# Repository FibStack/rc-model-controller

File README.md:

# RC Transmitter Receiver System

## Overview

This project has the design files for a custom Remote Control (RC) system that you can use to control different models. The design files include:

- Schematics and PCB design for the transmitter and receiver boards.
- The source code for the microcontrollers on the transmitter and receiver boards.
- A sample 3D printable model for an RC car.

Please note that this is just the initial proof of concept, and more updates are on the way to make it even better.

## Project organization

- **hardware/** - In this folder, you'll find the circuit schematics and PCB design files for both the receiver and transmitter boards.
- **software/attiny824-transmiter** - This contains the source code for the ATTiny824 chip on the transmitter board.
- **software/attiny824-receiver** - Here, you'll find the source code for the ATTiny824 chip on the receiver board.
- **rc-car-frame.FCStd** - This file holds a 3D model of an RC car frame that we used for testing in this project.

## Development tools

- **[Microchip Studio 7.0](https://www.microchip.com/en-us/tools-resources/develop/microchip-studio)**: The IDE for writing and building source code for the ATTiny chip. We also use this tool to flash the chips.
- **[ATMEL-ICE](https://www.microchip.com/en-us/development-tool/ATATMEL-ICE)**: Hardware tool for flashing ATTiny chips.
- **[KiCad EDA](https://www.kicad.org/)**: The application for schematic and PCB design.
- **[FreeCAD](https://www.freecad.org/)**: The application for parametric desing used to desing the model.

To build the ATTiny824 firmware, open the project in Microchip Studio. Build the solution to generate the `*.HEX` file. Next, use the appropriate tool available to flash the chip.

## BOM
| # | Components | Recommended models | Footprint | Quantity |
| --- | --- | --- | --- | --- |
| 1 | PCB | Recommended two-layer PCB board of 1.6 mm thickness | | 1 |
| 2 | U1, U2 | ATtiny824 | SOIC-14 | 2 |
| 3 | C1, C2 | 100nF | 0603 (1608 metric) | 2 |
| 4 | D1, D3 | SMD LED | 0603 (1608 metric) | 2 |
| 5 | D2, D4 | SMD Generic diode | MicroMELF | 2 |
| 6 | Q1-Q6 | 2N7002 | SOT-23 | 6 |
| 7 | R1, R2, R4, R5, R6, R7, R9, R12, R13, R18, R19, R20  | 10K | 0603 (1608 metric) | 12 |
| 8 | R3, R14  | 470 | 0603 (1608 metric) | 2 |
| 9 | R8, R10, R11, R15, R16, R17  | 100 | 0603 (1608 metric) | 6 |
| 10 | RV1 | 10K Slide Potentiometer | PTA1543 | 1 |
| 11 | RV2 | 10K Potentiometer | T-16H Single Horizontal | 1 |
| 12 | SW1, SW2, SW3, SW4, SW5, SW6 | SPDT Slide Switch | P2.54mm | 6 |
| 13 | J1 | Male Header Connector, 1x3, pitch 2.54mm | 	1x3 - P2.54mm | 1 |
| 14 | J2, J5, J6, J7, J9, J10, J11, J12, J13, J14, J15, J17, J18, J19 | Male Header Connector, 1x2, pitch 2.54mm | 	1x2 - P2.54mm | 14 |
| 15 | J3, J16 | Male Header Connector, 2x3, pitch 2.54mm | 	2x3 - P2.54mm | 2 |
| 16 | J8 | Male Header Connector, 1x4, pitch 2.54mm | 	1x4 - P2.54mm | 1 |

## Documentation

For more detailed information about the project, please visit the [project page](https://fibstack.com/projects/rc-model-controller/).

## License Information
This product is open source!

Please review the LICENSE.md file for license information. Distributed as-is; no warranty is given.

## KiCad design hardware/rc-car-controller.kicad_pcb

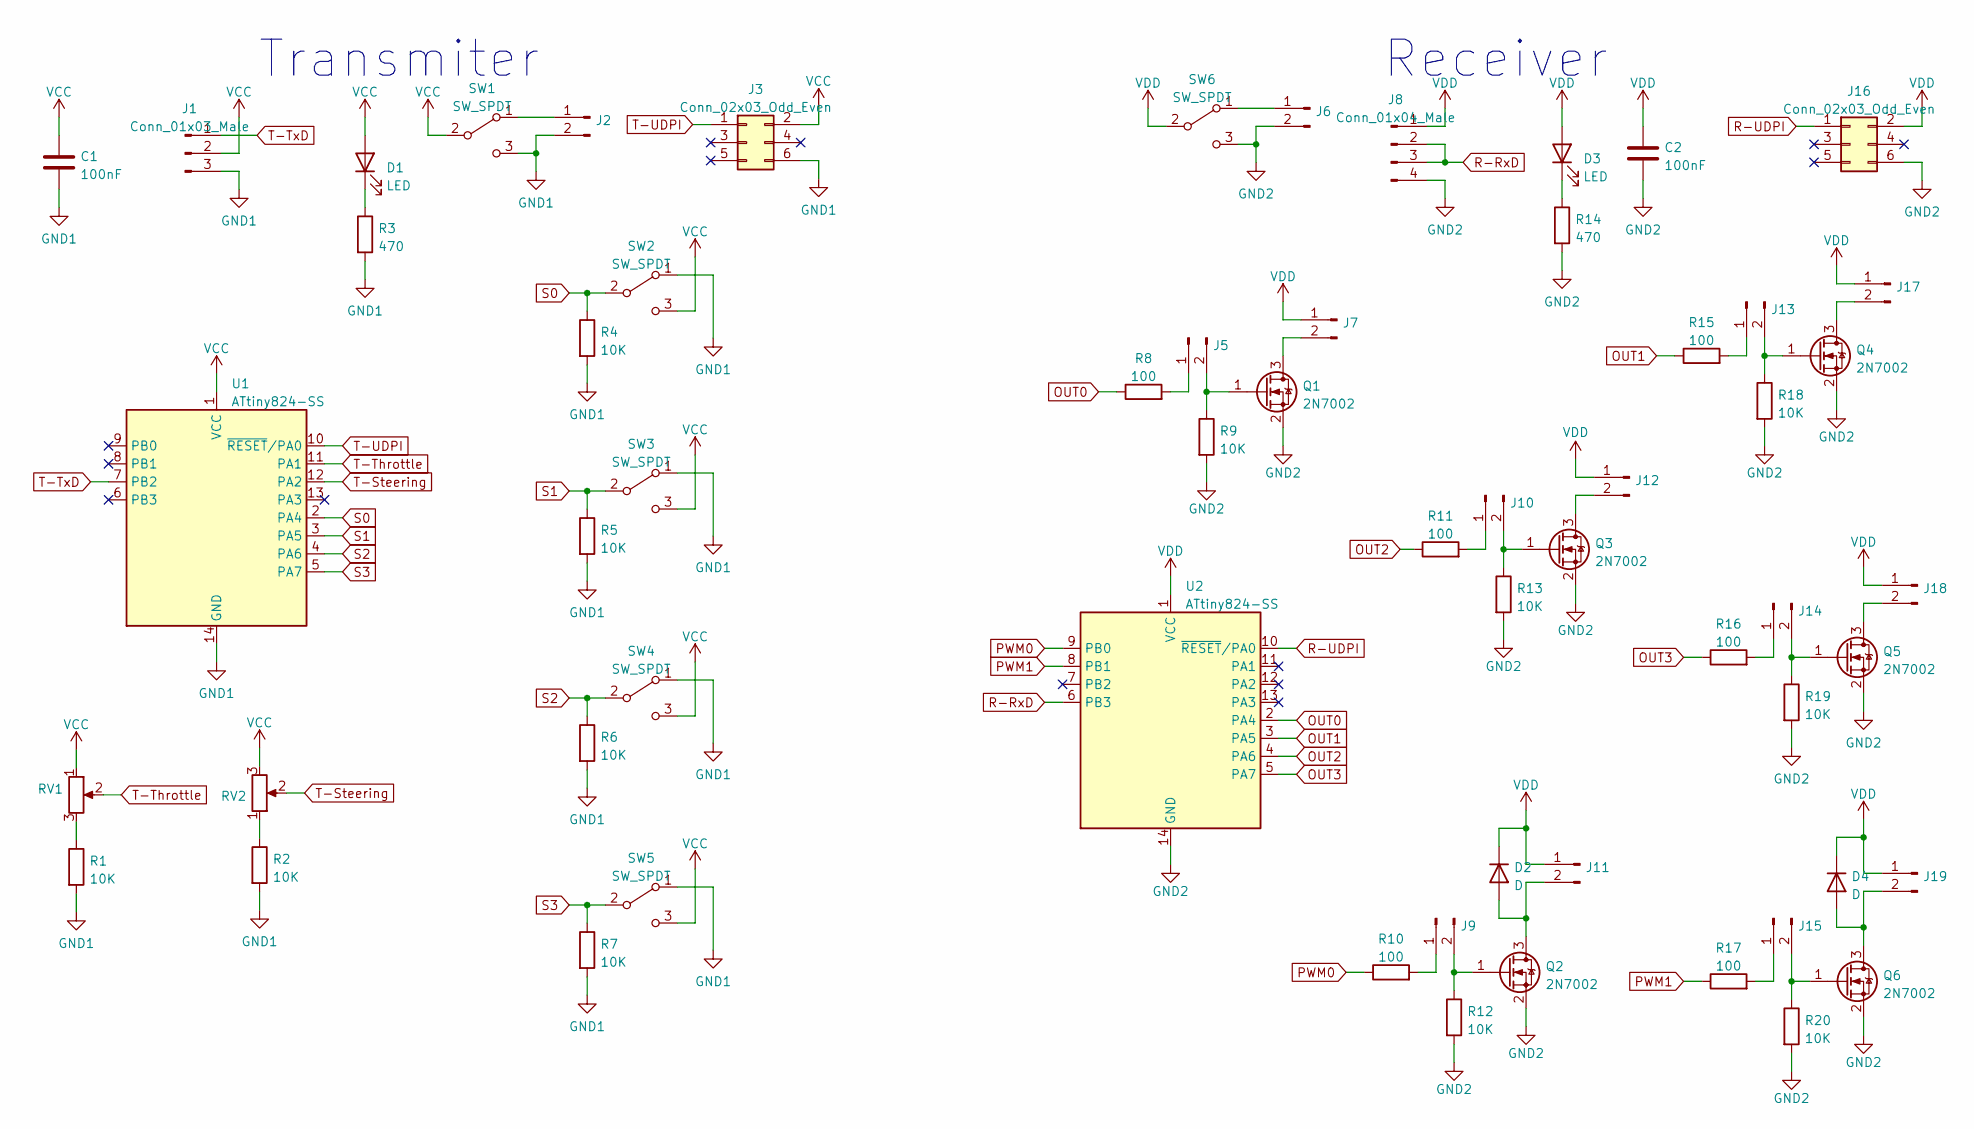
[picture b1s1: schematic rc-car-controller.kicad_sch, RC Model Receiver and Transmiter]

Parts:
C1, C2: 100nF; C_0603_1608Metric
D1, D3: LED; D_0603_1608Metric
D2, D4: D; D_MicroMELF
J1: Conn_01x03_Male; PinHeader_1x03_P2.54mm_Vertical
J2, J5, J6, J7, J9, J10, J11, J12, J13, J14, J15, J17, J18, J19: Conn_01x02_Male; PinHeader_1x02_P2.54mm_Vertical
J3, J16: Conn_02x03_Odd_Even; PinHeader_2x03_P2.54mm_Vertical
J8: Conn_01x04_Male; PinHeader_1x04_P2.54mm_Vertical
Q1, Q2, Q3, Q4, Q5, Q6: 2N7002; SOT-23
R1, R2, R4, R5, R6, R7, R9, R12, R13, R18, R19, R20: 10K; R_0603_1608Metric
R3, R14: 470; R_0603_1608Metric
R8, R10, R11, R15, R16, R17: 100; R_0603_1608Metric
RV1: R_Potentiometer; Potentiometer_Bourns_PTA1543_Single_Slide
RV2: R_Potentiometer; Potentiometer_Piher_T-16H_Single_Horizontal
SW1, SW2, SW3, SW4, SW5, SW6: SW_SPDT; PinHeader_1x03_P2.54mm_Vertical
U1, U2: ATtiny824-SS; SOIC-14_3.9x8.7mm_P1.27mm

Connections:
GND1: C1.2, J1.3, J2.2, J3.6, R1.2, R2.2, R3.2, R4.2, R5.2, R6.2, R7.2, SW1.3 (C), SW2.1 (A), SW3.1 (A), SW4.1 (A), SW5.1 (A), U1.14 (GND)
GND2: C2.2, J6.2, J8.4, J16.6, Q1.2 (S), Q2.2 (S), Q3.2 (S), Q4.2 (S), Q5.2 (S), Q6.2 (S), R9.2, R12.2, R13.2, R14.2, R18.2, R19.2, R20.2, SW6.3 (C), U2.14 (GND)
unnamed: D1.1 (K), R3.1
unnamed: D2.2 (A), J11.2, Q2.3 (D)
unnamed: D3.1 (K), R14.1
unnamed: D4.2 (A), J19.2, Q6.3 (D)
unnamed: J2.1, SW1.1 (A)
unnamed: J5.1, R8.2
unnamed: J5.2, Q1.1 (G), R9.1
unnamed: J6.1, SW6.1 (A)
unnamed: J7.2, Q1.3 (D)
unnamed: J9.1, R10.2
unnamed: J9.2, Q2.1 (G), R12.1
unnamed: J10.1, R11.2
unnamed: J10.2, Q3.1 (G), R13.1
unnamed: J12.2, Q3.3 (D)
unnamed: J13.1, R15.2
unnamed: J13.2, Q4.1 (G), R18.1
unnamed: J14.1, R16.2
unnamed: J14.2, Q5.1 (G), R19.1
unnamed: J15.1, R17.2
unnamed: J15.2, Q6.1 (G), R20.1
unnamed: J17.2, Q4.3 (D)
unnamed: J18.2, Q5.3 (D)
unnamed: R1.1, RV1.3
unnamed: R2.1, RV2.1
OUT0: R8.1, U2.2 (PA4)
OUT1: R15.1, U2.3 (PA5)
OUT2: R11.1, U2.4 (PA6)
OUT3: R16.1, U2.5 (PA7)
PWM0: R10.1, U2.9 (PB0)
PWM1: R17.1, U2.8 (PB1)
R-RxD: J8.2, J8.3, U2.6 (PB3)
R-UDPI: J16.1, U2.10 (~RESET/PA0)
S0: R4.1, SW2.2 (B), U1.2 (PA4)
S1: R5.1, SW3.2 (B), U1.3 (PA5)
S2: R6.1, SW4.2 (B), U1.4 (PA6)
S3: R7.1, SW5.2 (B), U1.5 (PA7)
T-Steering: RV2.2, U1.12 (PA2)
T-Throttle: RV1.2, U1.11 (PA1)
T-TxD: J1.1, U1.7 (PB2)
T-UDPI: J3.1, U1.10 (~RESET/PA0)
VCC: C1.1, D1.2 (A), J1.2, J3.2, RV1.1, RV2.3, SW1.2 (B), SW2.3 (C), SW3.3 (C), SW4.3 (C), SW5.3 (C), U1.1 (VCC)
VDD: C2.1, D2.1 (K), D3.2 (A), D4.1 (K), J7.1, J8.1, J11.1, J12.1, J16.2, J17.1, J18.1, J19.1, SW6.2 (B), U2.1 (VCC)

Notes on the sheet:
Receiver
Transmiter

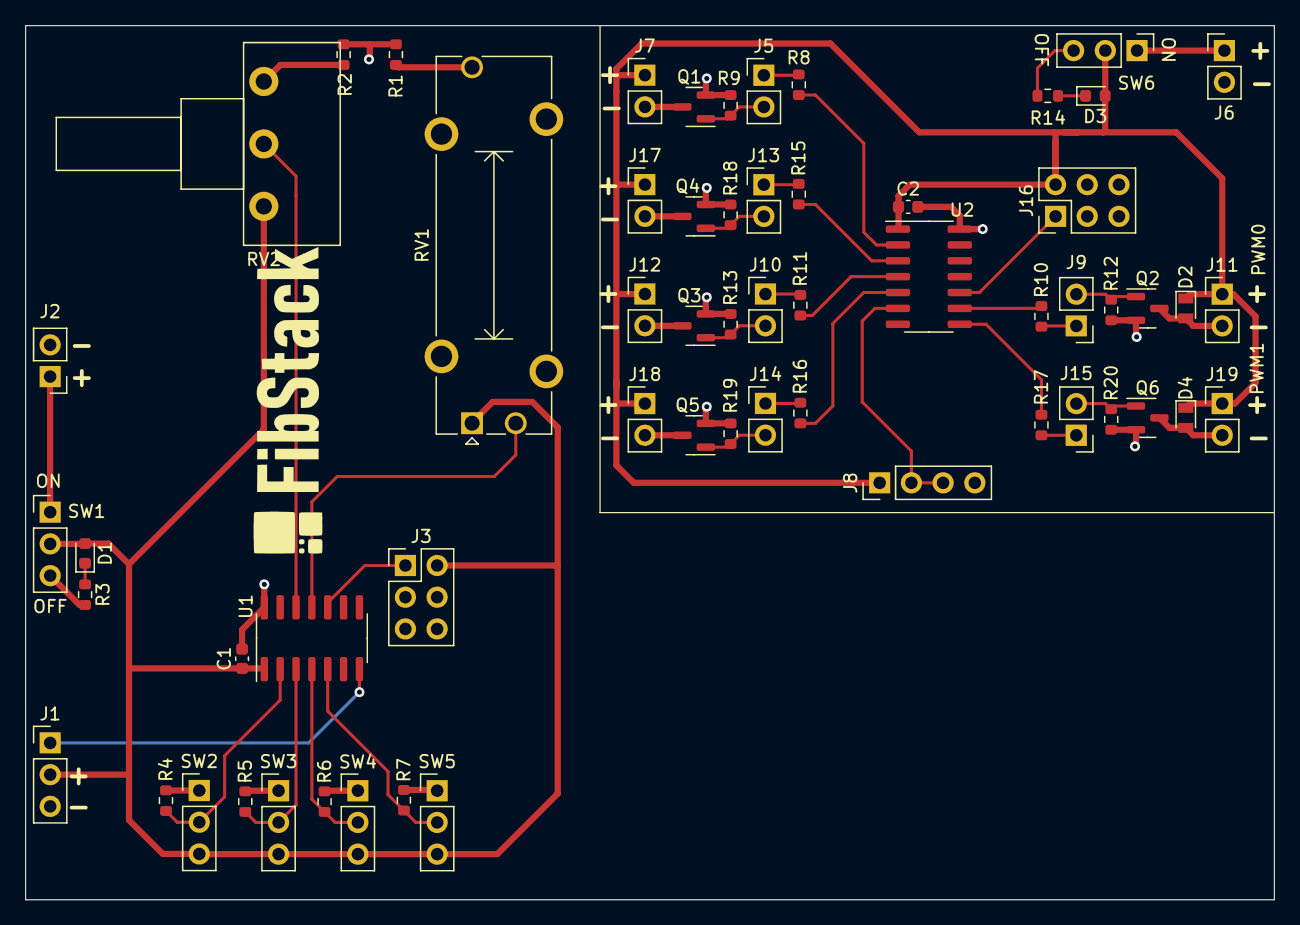
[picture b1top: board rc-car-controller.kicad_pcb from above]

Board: 2 copper layers, 100.0 x 70.0 mm, 60 parts (0 on the bottom side), 44 nets.

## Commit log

2023-10-12 Initial desing files
2023-10-12 fixed a line

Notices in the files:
hardware/rc-car-controller.kicad_pcb:
of the CERN-OHL-P V2 license (https:/cern.ch/cern-ohl).
Copyright © 2021-2023, FibStack
